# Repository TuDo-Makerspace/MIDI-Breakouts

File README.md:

# Just another pair of MIDI breakout boards <!-- omit in toc -->

## Table of Contents <!-- omit in toc -->

- [Overview & Background](#overview--background)
- [Noteworthy Features](#noteworthy-features)
- [Schematics](#schematics)
	- [MIDI IN](#midi-in)
	- [MIDI OUT](#midi-out)
- [Ordering](#ordering)
- [Parts & Assembly](#parts--assembly)
- [Pictures](#pictures)
- [License](#license)

## Overview & Background

This repository contains the KiCad files for a pair of MIDI breakout boards. There isn't anything particularly special about them, besides perhaps the fact that the MIDI OUT has a switch to select between 3.3V and 5V operation, as well as two BS170 MOSFETs to sink the current, rather than using buffer chips. Oh, and we use JST-XH connectors, because I hate those loose "DuPont" headers that allow you to plug things in the wrong way around! >:(

Further, one may also question the odd choice of some components, such as the 100nF film capacitor for voltage decoupling, instead of a 100nF ceramic capacitor.
This really leads us to why these boards have even been made in first place. They were really just intended as test boards to try out some [template MIDI schematics](https://github.com/TU-DO-Makerspace/KiCAD-MIDI-Templates) I designed for future projects that require MIDI support. The components were chosen according to the stuff we had lying around in our lab, hence the quirky choice of components and varying resistor footprints.

I'm still dumping this on GitHub, as we still have a few of these boards lying around and the repo serves as good documentation, but perhaps someone out there might also find them useful. After all, if you don't feel like using pricey film caps, you can always just pop in a ceramic one instead! The footprint is not that different!

## Noteworthy Features

MIDI IN:

 - Utilizes the faster 6N137 Optocoupler opposed to the more common 6N138
 - Uses a 15pF decoupling capacitor on the optocoupler's output for better noise immunity
 - Provides two parallel JST-XH connectors:
   - One to connect to the receiving device (eg. a MCU)
   - One to directly connect to a MIDI OUT board which gives you a MIDI THRU output

MIDI OUT:

 - Utilizes two BS170 MOSFETs to sink the current, rather than using buffer chips
 - Has a switch to select between 3.3V and 5V operation
 - Uses a JST XH connector to connect to the sending device (eg. a MCU, or a MIDI IN board for MIDI THRU)

Both boards are compliant with the MIDI Specification

## Schematics

### MIDI IN

### MIDI OUT

## Ordering

The directories for the individual boards contain a "Gerbers" directory, which contains the gerber files for the respective board. You can use these to order the boards from your desired PCB manufacturer.

## Parts & Assembly

An interactive BOM for both boards can be found [here](https://tu-do-makerspace.github.io/MIDI-Breakouts/)

The interactive bom contains a PCB view that allows you to see which components go where, and what value they have.
This is particularly useful to have open while assembling the boards.

## Pictures

## License

The following project is licensed under the [CERN-OHL-P v2 license](https://ohwr.org/cern_ohl_p_v2.pdf)

The boards on the pictures claim `TAPR Open Hardware License v1.0`, however, the KiCAD project has been updated to use the CERN-OHL-P v2 license.

Crediting is always appreciated, even for something as trivial as a pair of breakout boards!

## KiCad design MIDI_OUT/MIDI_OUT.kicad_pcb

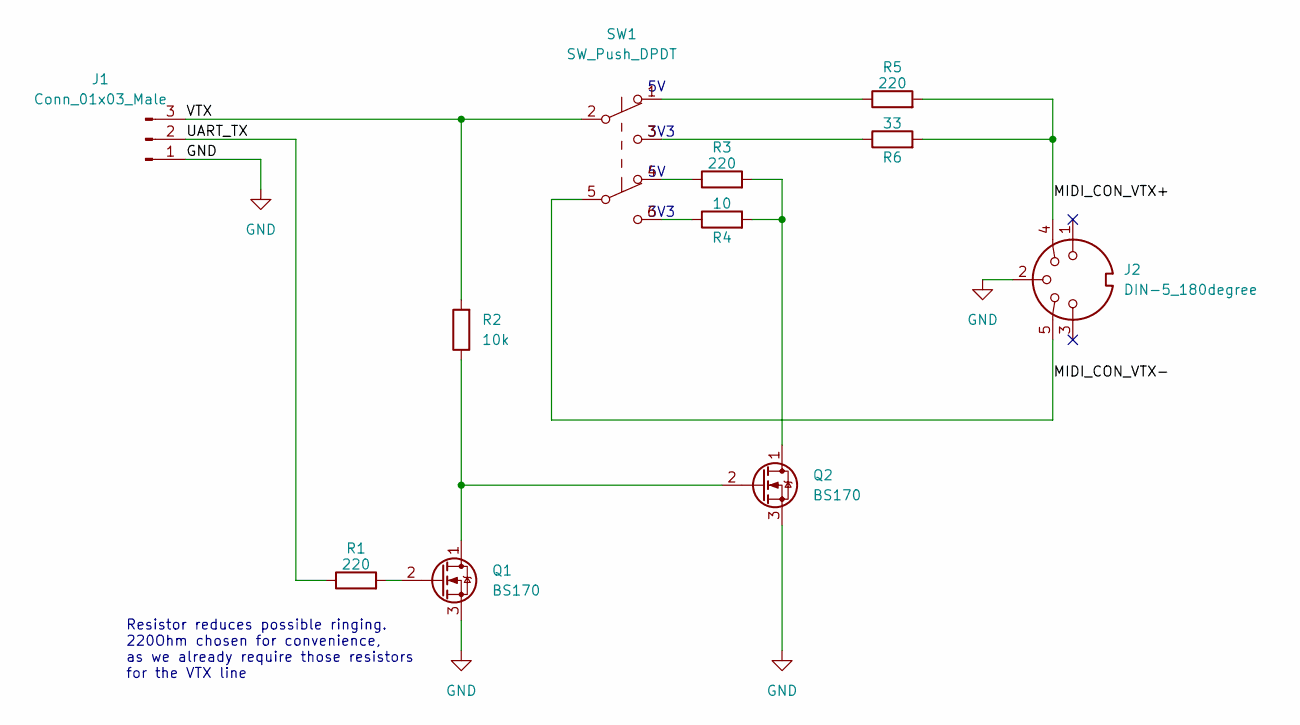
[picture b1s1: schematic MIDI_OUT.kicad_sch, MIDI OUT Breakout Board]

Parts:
J1: Conn_01x03_Male; JST_XH_B3B-XH-A_1x03_P2.50mm_Vertical
J2: DIN-5_180degree; MIDI_DIN5
Q1, Q2: BS170; TO-92L_Inline
R1, R3, R5: 220; R_Axial_DIN0207_L6.3mm_D2.5mm_P7.62mm_Horizontal
R2: 10k; R_Axial_DIN0204_L3.6mm_D1.6mm_P5.08mm_Horizontal
R4: 10; R_Axial_DIN0204_L3.6mm_D1.6mm_P5.08mm_Horizontal
R6: 33; R_Axial_DIN0207_L6.3mm_D2.5mm_P7.62mm_Horizontal
SW1: SW_Push_DPDT; SW_CuK_JS202011CQN_DPDT_Straight

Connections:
/MIDI_CON_VTX+: J2.4, R5.2, R6.2
/MIDI_CON_VTX-: J2.5, SW1.5 (B)
/UART_TX: J1.2, R1.1
/VTX: J1.3, R2.2, SW1.2 (B)
GND: J1.1, J2.2, Q1.3 (S), Q2.3 (S)
unnamed: Q1.1 (D), Q2.2 (G), R2.1
unnamed: Q1.2 (G), R1.2
unnamed: Q2.1 (D), R3.2, R4.2
unnamed: R3.1, SW1.4 (A)
unnamed: R4.1, SW1.6 (C)
unnamed: R5.1, SW1.1 (A)
unnamed: R6.1, SW1.3 (C)

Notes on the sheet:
3V3
Resistor reduces possible ringing. 220Ohm chosen for convenience, as we already require those resistors for the VTX line

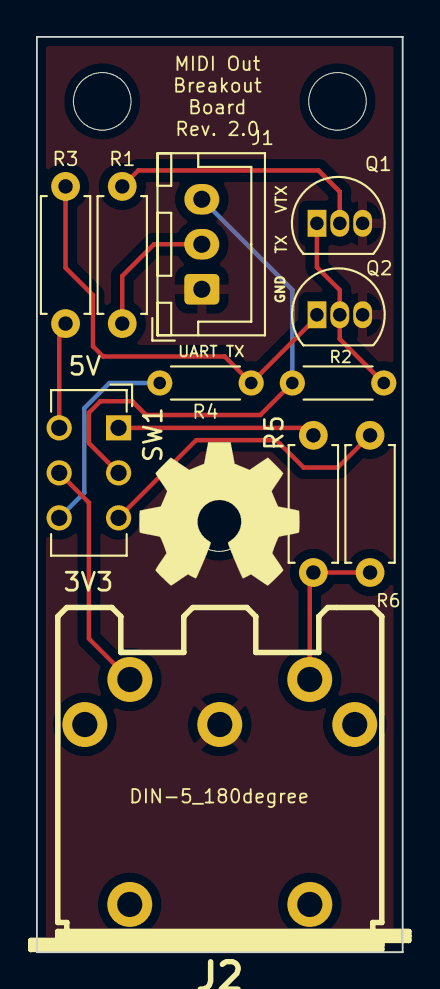
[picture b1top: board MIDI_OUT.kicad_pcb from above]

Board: 2 copper layers, 20.3 x 50.9 mm, 11 parts (0 on the bottom side), 12 nets.

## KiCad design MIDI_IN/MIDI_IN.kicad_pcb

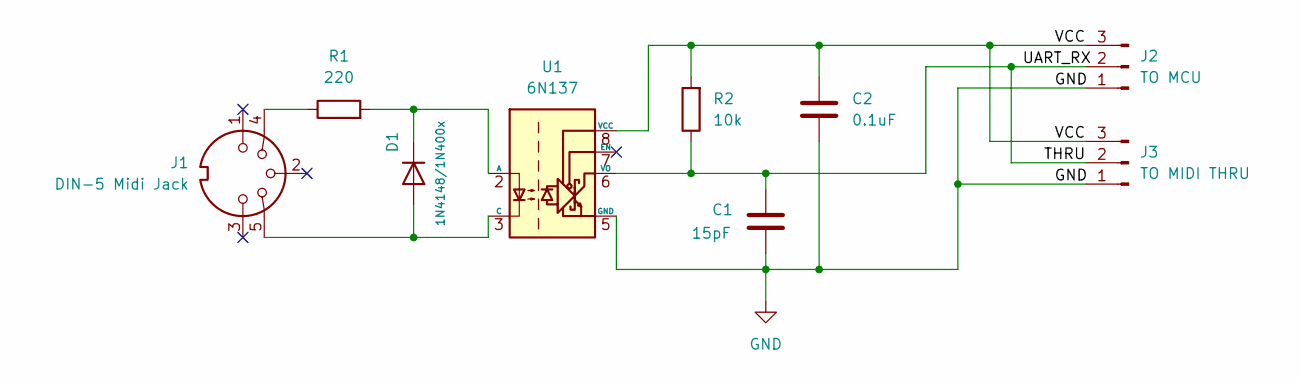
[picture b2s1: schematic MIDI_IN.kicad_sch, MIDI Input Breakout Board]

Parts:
C1: 15pF; C_Disc_D5.0mm_W2.5mm_P2.50mm
C2: 0.1uF; C_Rect_L10.0mm_W2.5mm_P7.50mm_MKS4
D1: 1N4148/1N400x; D_A-405_P7.62mm_Horizontal
J1: DIN-5 Midi Jack; MIDI_DIN5
J2: TO MCU; JST_XH_B3B-XH-A_1x03_P2.50mm_Vertical
J3: TO MIDI THRU; JST_XH_B3B-XH-A_1x03_P2.50mm_Vertical
R1: 220; R_Axial_DIN0207_L6.3mm_D2.5mm_P7.62mm_Horizontal
R2: 10k; R_Axial_DIN0204_L3.6mm_D1.6mm_P5.08mm_Horizontal
U1: 6N137; DIP-8_W7.62mm

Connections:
/THRU: C1.1, J2.2, J3.2, R2.1, U1.6 (VO)
/VCC: C2.1, J2.3, J3.3, R2.2, U1.8 (VCC)
GND: C1.2, C2.2, J2.1, J3.1, U1.5 (GND)
unnamed: D1.1 (K), R1.2, U1.2 (A)
unnamed: D1.2 (A), J1.5, U1.3 (C)
unnamed: J1.4, R1.1

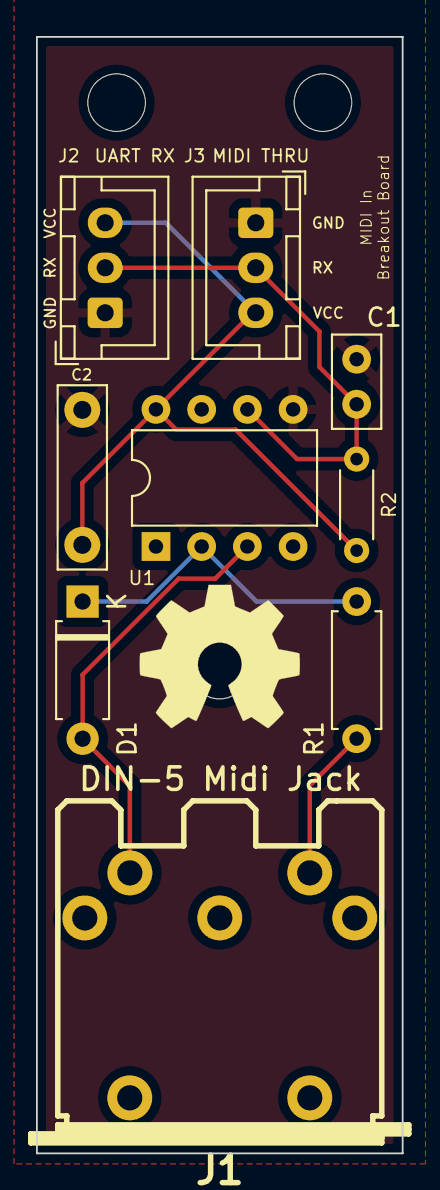
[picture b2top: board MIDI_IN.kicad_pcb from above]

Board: 2 copper layers, 20.3 x 62.0 mm, 9 parts (0 on the bottom side), 6 nets.

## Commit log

2022-10-13 Initial commit of v0.0.1
2022-11-14 Added README
2022-11-14 Updated license to CERN-OHL-P v2 license
2022-11-14 README: Added link to template schematics
2022-11-14 README: Minor change
2022-11-14 README: Added schematics
2022-11-14 MIDI_OUT: Removed gerbers zip
2022-11-14 README: Fixed img not displaying
2022-11-14 README: Added title for TOC
2022-11-15 Added posters to repo
2022-11-15 README: Move title pic to pictures section + minor changes
2022-11-15 Posters: Added positive poster
2022-11-24 Added index html page for github pages
2022-11-24 Github Pages: Created index page
2022-11-24 GitHub Pages: Copied iboms to docs/
2022-11-24 README: Updated Assembly part
2022-11-24 README: Small fix

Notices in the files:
MIDI_IN/MIDI_IN.kicad_pcb:
License: CERN-OHL-P v2
Licensed under CERN-OHL-P v2
